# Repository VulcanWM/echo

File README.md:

# Echo

This is my first hardware project, in which I made a Simon Says game by designing a PCB and writing the firmware for it.

The components involved are a XIAO RP2040 as the microcontroller, 3 switches which represent the possible options the player has to press, 3 different coloured LEDs that light up when introducing the sequence, resistors to stop the LEDs from receiving too much current, and a buzzer so the game is not just vision-based but also audio-based.

There is also a CAD-designed case, consisting only of a bottom section. I felt that a top cover was unnecessary, as the buttons and LEDs need to remain clearly visible and accessible. The bottom case mainly protects the PCB while making the device easier and more comfortable to hold. There are 4 mounting holes so that the PCB can be securely attached to standoffs in the case using screws.

How the game works is:
- You press any button to start.
- It gives you a sequence of length 1 (while playing a tone and lighting up the corresponding LED).
- You then have to press the button that corresponds to the LED that just lit up.
- If you get that right, you are given a sequence of length 2, with one extra note added to the previous sequence.
- The game keeps going until you either get the sequence wrong (and hear a losing tune I created), or reach 100 rounds (and hear a victory tune I created).

I made it because I spend a lot of time on devices, so whenever I've been using one continuously for around an hour, I can take a break by playing this game. Since it's a memory game, it also helps me improve my focus.

## Images

The KiCad source files (`.kicad_pro`, `.kicad_sch`, `.kicad_pcb`) and `gerbers.zip` used to manufacture the PCB are located in the [`pcb-files`](pcb-files) folder.

This is what the schematic looks like:

This is what the PCB looks like:

This is what the PCB looks like in the 3D renderer:

The Fusion CAD source files (`.step`, `.stl`, `.f3d`) used to manufacture the case can be found in the [`case-files`](case-files) folder.

This is what the case looks like (with the PCB inside it):

## Firmware

The firmware contains the code for exactly what I explained in the how the game works' section and it was written in the Arduino IDE in C++. It is in the [echo.ino](https://github.com/VulcanWM/echo/blob/main/echo.ino) file.

## Assembly
1. Order the PCB using the Gerber files in the pcb-files folder and 3D print the bottom case using the files in the case-files folder. 
2. Solder the XIAO RP2040, 3 LEDs, 3 resistors, buzzer, and 3 switches onto the PCB, making sure the LEDs are inserted with the correct polarity.
3. Place the keycaps onto the three switches.
4. Position the PCB on top of the four standoffs in the case, lining up the 2.2mm PCB mounting holes with the pilot holes in the standoffs.
5. Use M2 self-tapping screws to secure the PCB to the case. The screws thread into the 1.7mm pilot holes in the standoffs.
6. Check that the XIAO RP2040 USB-C port lines up with the cutout in the side of the case and that no components or solder joints are touching the bottom of the case.
7. Connect the XIAO RP2040 over USB-C and upload the firmware from `echo.ino`.
8. Test each switch, LED, and the buzzer before playing the game.

## BOM
(Also in the [BOM.csv](https://github.com/VulcanWM/echo/blob/main/BOM.csv) file)

| Name                                        | Qty | Link |       Cost |
|---------------------------------------------|----:|------|-----------:|
| Seeed Studio XIAO RP2040                    | 1 | https://www.seeedstudio.com/XIAO-RP2040-v1-0-p-5026.html |      $3.90 |
| Gateron Milky Pro Yellow Switches (10-pack) | 1 | https://www.aliexpress.com/item/1005004061195309.html |      $4.25 |
| DSA PBT 1U Keycaps (10-pack)                | 1 | https://www.aliexpress.com/item/1005012418077180.html?spm=a2g0o.productlist.main.44.2c60uVRtuVRtVY&algo_pvid=b6b50a2a-433e-464b-94e8-dcf3317d2a18&algo_exp_id=b6b50a2a-433e-464b-94e8-dcf3317d2a18-43&pdp_ext_f=%7B%22order%22%3A%227%22%2C%22eval%22%3A%221%22%2C%22fromPage%22%3A%22search%22%7D&pdp_npi=6%40dis%21GBP%215.35%212.56%21%21%2146.85%2122.40%21%402103849717854356457228356e0d1a%2112000058315981392%21sea%21UK%210%21ABX%211%210%21n_tag%3A-29910%3Bd%3Acec8671b%3Bm03_new_user%3A-29895%3BpisId%3A5000000211438706&curPageLogUid=owTJvLrJ00ZO&utparam-url=scene%3Asearch%7Cquery_from%3A%7Cx_object_id%3A1005012418077180%7C_p_origin_prod%3A |      $7.21 |
| 5mm Red LED                                 | 1 | https://www.lcsc.com/product-detail/C52034661.html?s_z=n_q_5A4RUD&spm=wm.fly.bg.0.xh&lcsc_vid=QFQKVFAHRFdWVwBXQQdeU1IFFFddUQJQRlNXBlRQT1IxVlNeQlVdUlBfQVJYVjsOAxUeFF5JWBYZEEoKFBINSQcJGk4dAgUUFAk%3D |      $0.41 |
| 5mm Blue LED                                | 1 | https://www.lcsc.com/product-detail/C52034724.html?s_z=s_p_5A4BUD&spm=wm.fly.bg.0.xh&lcsc_vid=QFQKVFAHRFdWVwBXQQdeU1IFFFddUQJQRlNXBlRQT1IxVlNeQlVdUlFeQFhWUTsOAxUeFF5JWBYZEEoKFBINSQcJGk4dAgUUFAk%3D |      $0.64 |
| 5mm Yellow LED                              | 1 | https://www.lcsc.com/product-detail/C52034720.html?s_z=s_p_5A4YUD&spm=wm.fly.bg.0.xh&lcsc_vid=QFQKVFAHRFdWVwBXQQdeU1IFFFddUQJQRlNXBlRQT1IxVlNeQlVdUlFSQ1ZZUTsOAxUeFF5JWBYZEEoKFBINSQcJGk4dAgUUFAk%3D |      $0.57 |
| 220Ω 1/4W Through-Hole Resistor (50-pack)   | 1 | https://www.lcsc.com/product-detail/C127220.html?s_z=n_q_p_220%25CE%25A9%25201%252F4W%2520Through-Hole%2520Resistor&spm=wm.ssy.bg.2.xh&lcsc_vid=QFQKVFAHRFdWVwBXQQdeU1IFFFddUQJQRlNXBlRQT1IxVlNeQlVdU1xVT1hZVjsOAxUeFF5JWBYZEEoKFBINSQcJGk4dAgUUFAk%3D |      $0.57 |
| TDK PS1240P02BT Piezo Transducer            | 1 | https://www.lcsc.com/product-detail/C76871.html?s_z=n_q_p_TDK%2520PS1240P02BT%2520Piezo%2520Transducer&spm=wm.ssy.bg.0.xh&lcsc_vid=QFQKVFAHRFdWVwBXQQdeU1IFFFddUQJQRlNXBlRQT1IxVlNeQlVdU1JfQVBcXjsOAxUeFF5JWBYZEEoKFBINSQcJGk4dAgUUFAk%3D |      $0.22 |
| Custom PCB (5 boards)                       | 1 | https://jlcpcb.com |      $4.00 |
| Shipping                                    | 1 | https://jlcpcb.com |     ~$3.50 |
| **Estimated Total**                         |  |  | **~$25.27** |

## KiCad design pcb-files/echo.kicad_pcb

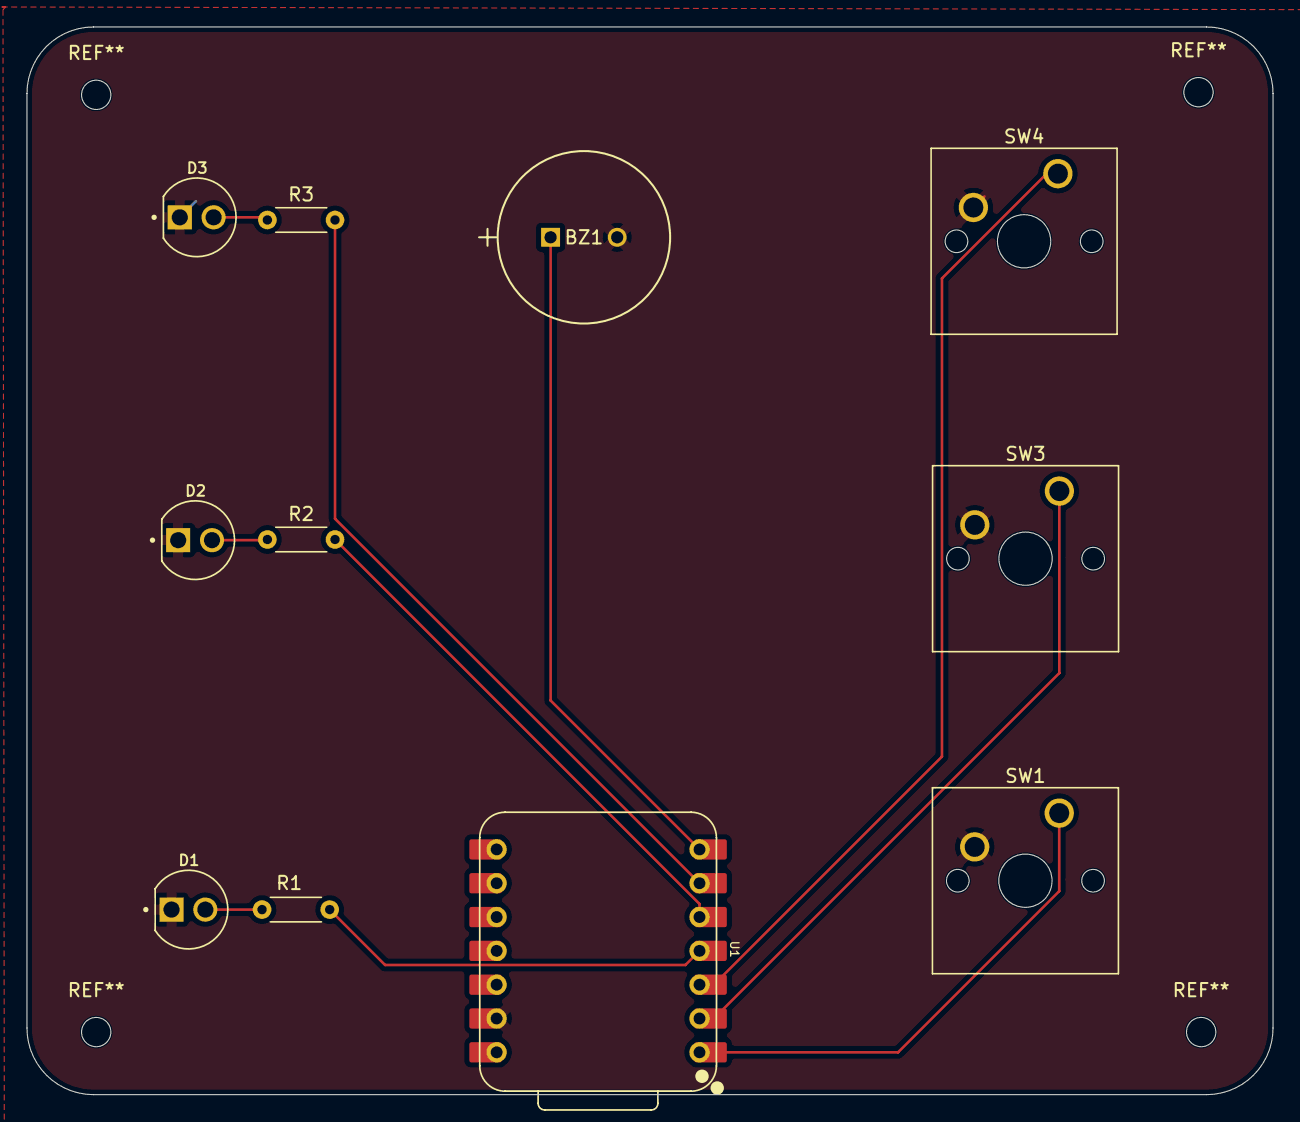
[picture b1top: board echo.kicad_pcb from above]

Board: 2 copper layers, 93.6 x 80.2 mm, 11 parts (0 on the bottom side), 11 nets.

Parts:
BZ1: PS1240P02BT; XTAL_PS1240P02BT_TDK
D1, D2, D3: L08R5000Q1; LEDRD254W57D500H1070
R1, R2, R3: R; R_Axial_DIN0204_L3.6mm_D1.6mm_P5.08mm_Horizontal
SW1, SW3, SW4: SW_Push; SW_Cherry_MX_1.00u_PCB
U1: XIAO-RP2040-SMD; XIAO-RP2040-DIP

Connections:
GND: BZ1.2, D1.C, D2.C, D3.C, SW1.2, SW3.2, SW4.2, U1.13 (GND)
unnamed: D1.A, R1.1
unnamed: D2.A, R2.1
unnamed: D3.A, R3.1
button1: SW1.1, U1.1 (D0)
button2: SW3.1, U1.2 (D1)
button3: SW4.1, U1.3 (D2)
buzzer: BZ1.1, U1.7 (D6)
led1: R1.2, U1.4 (D3)
led2: R2.2, U1.5 (D4)
led3: R3.2, U1.6 (D5)

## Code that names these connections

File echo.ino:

int button1 = D0;
int button2 = D1;
int button3 = D2;

int led1 = D3;
int led2 = D4;
int led3 = D5;
int leds[] = {led1, led2, led3};

int buzzer1 = D6;

bool gameStarted = false;
int round = 0;

int sequence[100]; // win at 100
int inputIndex = 0;

void newRound(){
  delay(500);
  
  int newColour = random(3);
  sequence[round-1] = newColour;
  for (int i = 0; i < round; i++){
    int currentColour = sequence[i];
    int frequency = (currentColour+1) * 300;
    tone(buzzer1, frequency, 1000);
    digitalWrite(leds[currentColour], HIGH);
    delay(1000);
    digitalWrite(leds[currentColour], LOW);
    if (i != (round-1)){
      delay(500);
    }
  }
}

void loseTune(){
  tone(buzzer1, 900, 500);
  delay(500);
  tone(buzzer1, 800, 500);
  delay(500);
  tone(buzzer1, 700, 500);
  delay(500);
  tone(buzzer1, 600, 500);
  delay(500);
  tone(buzzer1, 500, 1000);
  delay(1000);
}

void victoryTune(){
  tone(buzzer1, 500, 500);
  delay(500);
  tone(buzzer1, 600, 500);
  delay(500);
  tone(buzzer1, 700, 500);
  delay(500);
  tone(buzzer1, 800, 500);
  delay(500);
  tone(buzzer1, 900, 500);
  delay(500);
  tone(buzzer1, 900, 500);
  delay(500);
  tone(buzzer1, 900, 500);
  delay(500);
}

void waitForRelease() {
  while (
    digitalRead(button1) == LOW ||
    digitalRead(button2) == LOW ||
    digitalRead(button3) == LOW
  ) {
    delay(5);
  }

  delay(20);
}

void setup() {
  pinMode(button1, INPUT_PULLUP);
  pinMode(button2, INPUT_PULLUP);
  pinMode(button3, INPUT_PULLUP);

  pinMode(led1, OUTPUT);
  pinMode(led2, OUTPUT);
  pinMode(led3, OUTPUT);

  pinMode(buzzer1, OUTPUT);

  Serial.begin(9600);

  randomSeed(analogRead(0));
}

void loop() {
  if (gameStarted == false) {
    if (digitalRead(button1) == LOW || digitalRead(button2) == LOW || digitalRead(button3) == LOW){
      round = 1;
      gameStarted = true;
      newRound();
      inputIndex = 0;
      waitForRelease();
    }
  } else {
    bool buttonPressed = false;
    int pressedButton = 0;
    if (digitalRead(button1) == LOW){
      buttonPressed = true;
      pressedButton = 0;
    } else if (digitalRead(button2) == LOW){
      buttonPressed = true;
      pressedButton = 1;
    } else if (digitalRead(button3) == LOW){
      buttonPressed = true;
      pressedButton = 2;
    }

    if (buttonPressed == true){
      int frequency = (pressedButton+1)*300;
      if (sequence[inputIndex] == pressedButton){
        inputIndex += 1;
        tone(buzzer1, frequency, 500);
        digitalWrite(leds[pressedButton], HIGH);
        delay(500);
        digitalWrite(leds[pressedButton], LOW);
        waitForRelease();
        if (inputIndex == round){
          if (round == 100){
            victoryTune();
            gameStarted = false;
            return;
          }
          round += 1;
          inputIndex = 0;
          newRound();
        }
      } else {
        for (int i = 0; i < round; i++){
          int currentColour = sequence[i];
          int frequency = (currentColour+1) * 300;
          tone(buzzer1, frequency, 500);
          digitalWrite(leds[currentColour], HIGH);
          delay(500);
          digitalWrite(leds[currentColour], LOW);
          if (i != (round-1)){
            delay(250);
          }
        }
        loseTune();
        gameStarted = false;
      }
    }

    waitForRelease();
  }
}
